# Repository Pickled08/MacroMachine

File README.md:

This is a MacroPad Desgined with help from HackClub Blueprints Hackpad. My Design uses 6 mx switches with 4 indicator leds and an info screen to quickly preform actions on my desktop and pull any interesing info on the the OLED Screen

This is my first time using KiCad to create custom PCBs as well as using Fusion360, I am using this as an opertunity to learn design software so I can eventualy start creating fully custom projects in the Future

!!Ignoure OPL_Kicad_Library, KiCad-SSD1309-... and MacroMachine-Kicad only look at MacroMachine dir as all realvent files are there

BOM:

6x Cherry MX Switches
4x SK6812 MINI Leds
1x XIAO RP2040
1x SSD1306 0.91 inch OLED Screen
6x Blank DSA Keycaps
4x M3x16 Bolt
4x M3 Heatset

Case:

PCB:

PCB Schem:

Full:

Final:

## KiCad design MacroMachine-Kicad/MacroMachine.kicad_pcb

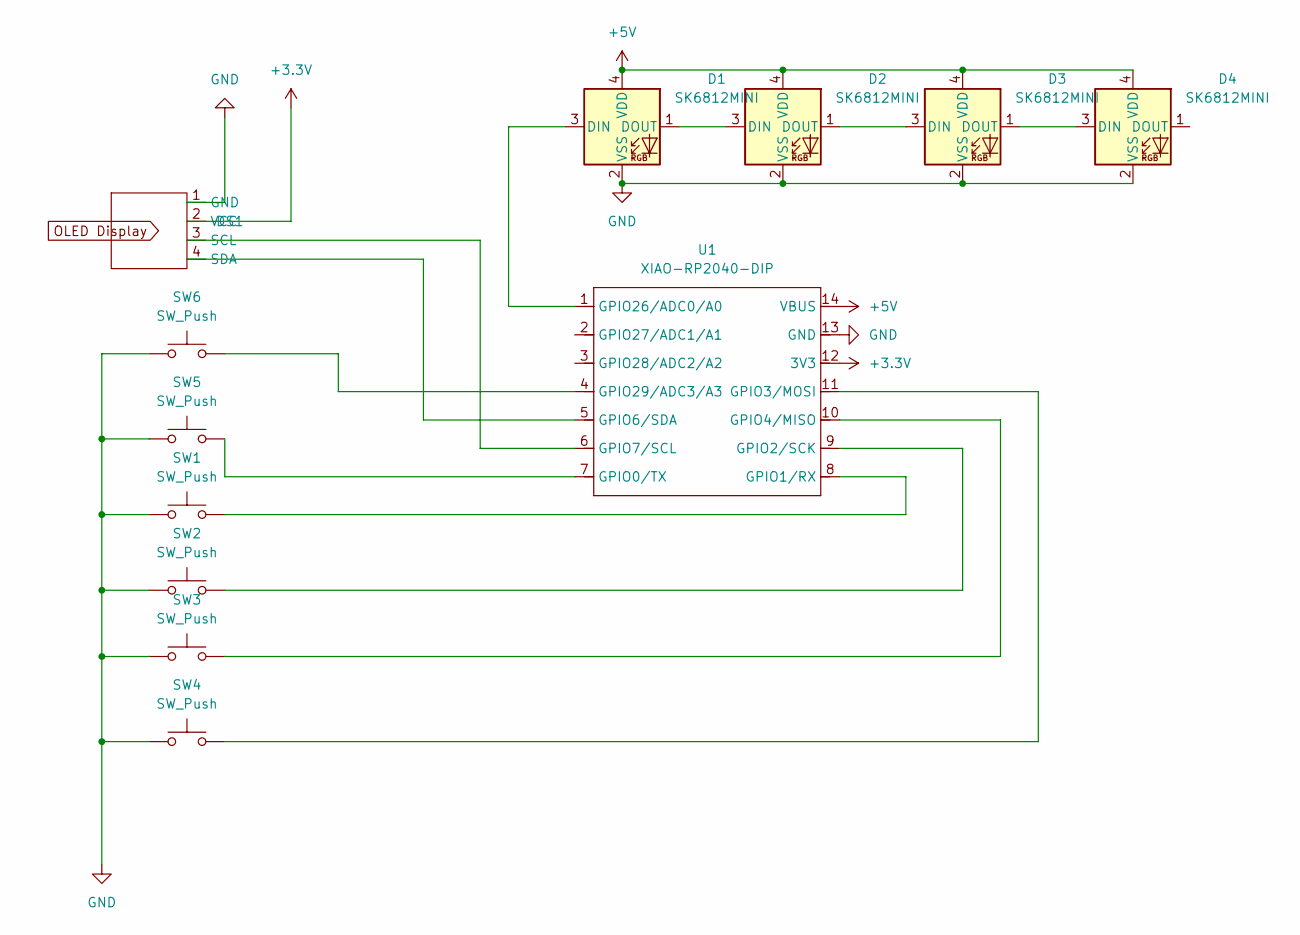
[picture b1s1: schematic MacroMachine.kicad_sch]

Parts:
D1, D2, D3, D4: SK6812MINI; LED_SK6812MINI_PLCC4_3.5x3.5mm_P1.75mm
DS1: SSD1306-0.91-OLED-4pin-128x32
SW1, SW2, SW3, SW4, SW5, SW6: SW_Push; SW_Cherry_MX_1.00u_PCB
U1: XIAO-RP2040-DIP; XIAO-RP2040-SMD

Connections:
+3.3V: DS1.2 (VCC), U1.12 (3V3)
+5V: D1.4 (VDD), D2.4 (VDD), D3.4 (VDD), D4.4 (VDD), U1.14 (VBUS)
GND: D1.2 (VSS), D2.2 (VSS), D3.2 (VSS), D4.2 (VSS), DS1.1 (GND), SW1.1, SW2.1, SW3.1, SW4.1, SW5.1, SW6.1, U1.13 (GND)
unnamed: D1.3 (DIN), U1.1 (GPIO26/ADC0/A0)
unnamed: D1.1 (DOUT), D2.3 (DIN)
unnamed: D2.1 (DOUT), D3.3 (DIN)
unnamed: D3.1 (DOUT), D4.3 (DIN)
unnamed: DS1.3 (SCL), U1.6 (GPIO7/SCL)
unnamed: DS1.4 (SDA), U1.5 (GPIO6/SDA)
unnamed: SW5.2, U1.7 (GPIO0/TX)
unnamed: SW1.2, U1.8 (GPIO1/RX)
unnamed: SW2.2, U1.9 (GPIO2/SCK)
unnamed: SW4.2, U1.11 (GPIO3/MOSI)
unnamed: SW3.2, U1.10 (GPIO4/MISO)
unnamed: SW6.2, U1.4 (GPIO29/ADC3/A3)

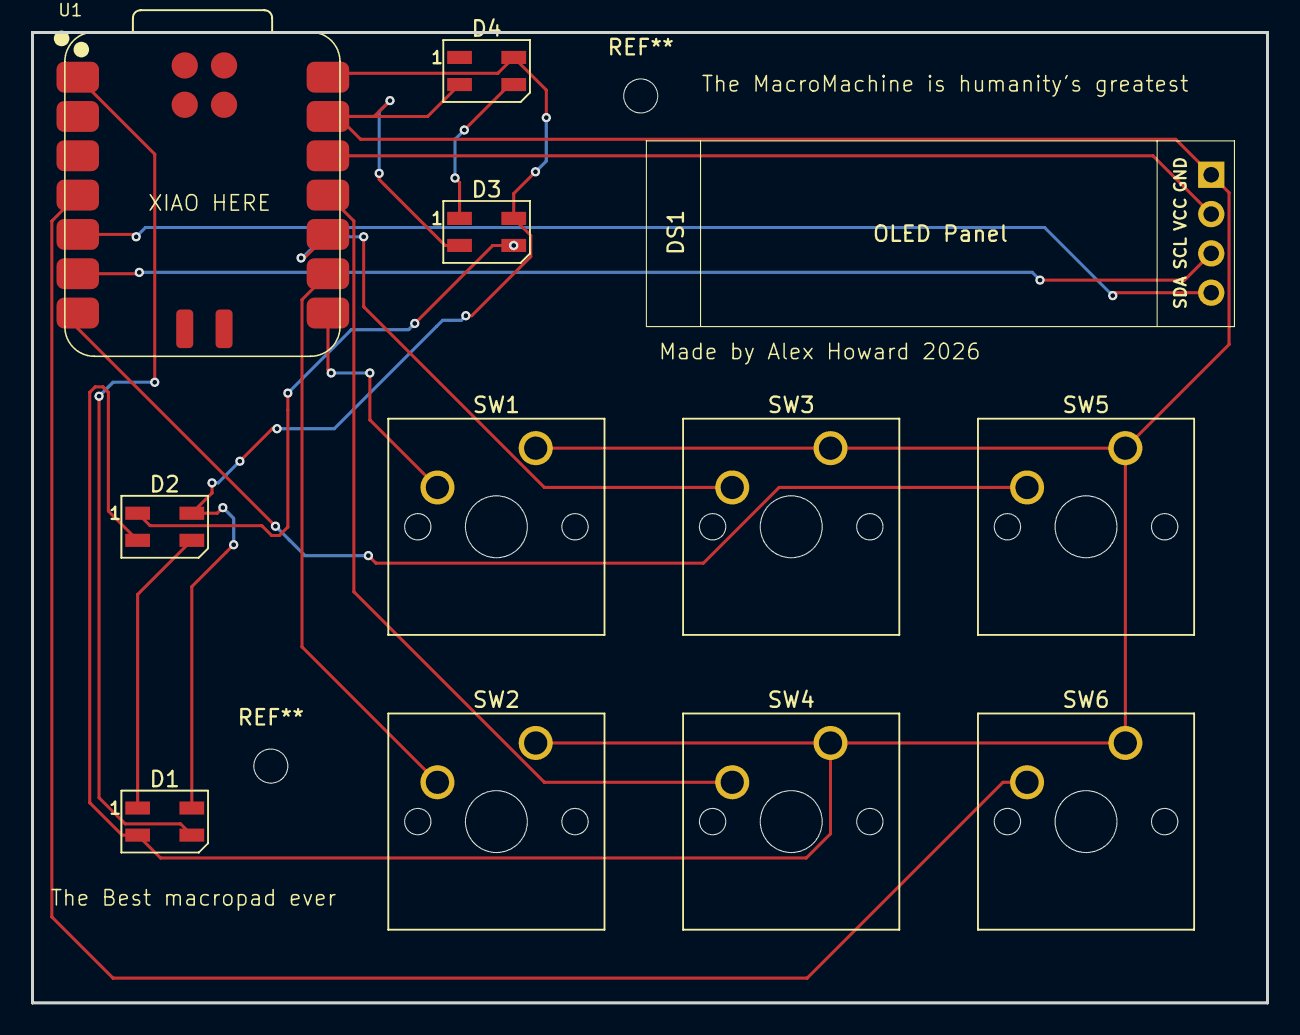
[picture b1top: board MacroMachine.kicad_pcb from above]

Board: 2 copper layers, 79.8 x 62.7 mm, 12 parts (0 on the bottom side), 15 nets.

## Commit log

2026-01-07 Innit
2026-01-07 edit digital pinout
2026-01-07 MacroMachine/~MacroMachine.kicad_sch.lck
2026-01-08 update for review
2026-01-14 gerber, stl
2026-02-07 Code/macropad/macropad.inoCode/localdriver.py
2026-02-11 Re added README
    Added a detailed description of the MacroPad project, including components, design software used, and images of the case and PCB.
2026-02-11 README.md
2026-02-11 readme
